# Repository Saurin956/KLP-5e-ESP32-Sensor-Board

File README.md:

# KLP-5e ESP32-C3 Sensor Board

> **Learning Recreation Project**

This is a learning recreation of the **KLP-5e ESP32-C3 4-layer IoT sensor board**. The schematic and PCB were recreated in KiCad by following the **Tech Explorations** tutorial. The resulting design closely follows the original reference project and was created to gain hands-on experience with a professional multilayer PCB design workflow.

## Project Status

* [x] Schematic recreated
* [x] 4-layer PCB layout completed
* [x] Design Rule Check (DRC) completed
* [x] Gerber and drill files generated
* [x] DFM/Gerber review completed
* [ ] PCB manufactured
* [ ] Hardware assembled
* [ ] Hardware tested

> The PCB design is complete, but this recreation has **not yet been manufactured, assembled, or hardware tested by me**.

## Overview

This project focuses on learning professional **4-layer PCB design** using KiCad through the recreation of an ESP32-C3 based IoT development board. The design integrates wireless connectivity, battery charging, environmental sensing, storage interfaces, display connectivity, and power management into a compact multilayer PCB.

The objective of this project was to understand the complete PCB design workflow, including schematic capture, component placement, multilayer routing, design validation, and manufacturing file generation.

## Board Features

* ESP32-C3-02 microcontroller with Wi-Fi and Bluetooth Low Energy
* 4-layer PCB stackup
* USB-C connector for power and programming interface
* TP4056 single-cell Li-ion battery charging circuit
* LiPo battery connector
* BME280 temperature, humidity, and pressure sensor
* Ambient light sensing
* Sound sensing circuit
* MicroSD card interface for data storage
* External flash memory
* I²C OLED display interface
* GPIO expansion interfaces
* Status LEDs and boot/reset circuitry
* Generated Gerber and drill files for manufacturing

## Learning Objectives

During this project, I practiced and learned:

* KiCad schematic design
* Hierarchical schematic organization
* 4-layer PCB stackup design
* Component placement and footprint selection
* Power distribution and grounding
* Decoupling capacitor placement
* Signal routing across multiple copper layers
* I²C and SPI peripheral integration
* USB and power management layout considerations
* Design Rule Checking (DRC)
* Gerber generation
* Drill file generation
* Design for Manufacturing (DFM) review

## Repository Structure

```text
.
├── Images/
│   └── PCB-3DView.png
│
├── KiCad 9 Esp32 Demo Project.kicad_pro
├── KiCad 9 Esp32 Demo Project.kicad_sch
├── KiCad 9 Esp32 Demo Project.kicad_pcb
│
├── esp32-c3-02.kicad_sch
├── sensors.kicad_sch
├── user_interface.kicad_sch
│
├── dfm/
│   └── gerber/
│
└── Esp32Project/
    └── Manufacturing output files
```

## Manufacturing Files

The repository includes generated manufacturing outputs such as:

* Gerber copper layers
* Solder mask layers
* Silkscreen layers
* Paste layers
* Board outline
* PTH and NPTH drill files
* Gerber job file

These files were generated as part of the KiCad PCB design workflow and reviewed during the learning exercise.

## Tools Used

* **KiCad 10** (project originally started in KiCad 9)
* ESP32-C3 hardware platform
* PCB Layout Editor
* Schematic Editor
* Gerber Viewer
* DRC and DFM tools

## Credits

This project is a **learning recreation** based on the original **KLP-5e ESP32-C3 Sensor Board** and the accompanying KiCad tutorial by **Tech Explorations (Peter Dalmaris)**.

* Original tutorial: Tech Explorations
* Original reference repository: `futureshocked/KLP-5e-ESP32-sensor-board`

I do **not** claim the original circuit or PCB design as my own. This repository documents my recreation and learning process using KiCad. The original project includes further design improvements, manufacturing, assembly, and hardware testing that are not yet part of my recreation.

## Future Work

* Make design improvements and explore possible modifications
* Manufacture the PCB
* Assemble the components
* Perform bring-up and hardware testing
* Validate power, charging, sensors, and storage interfaces
* Document testing results and board photographs

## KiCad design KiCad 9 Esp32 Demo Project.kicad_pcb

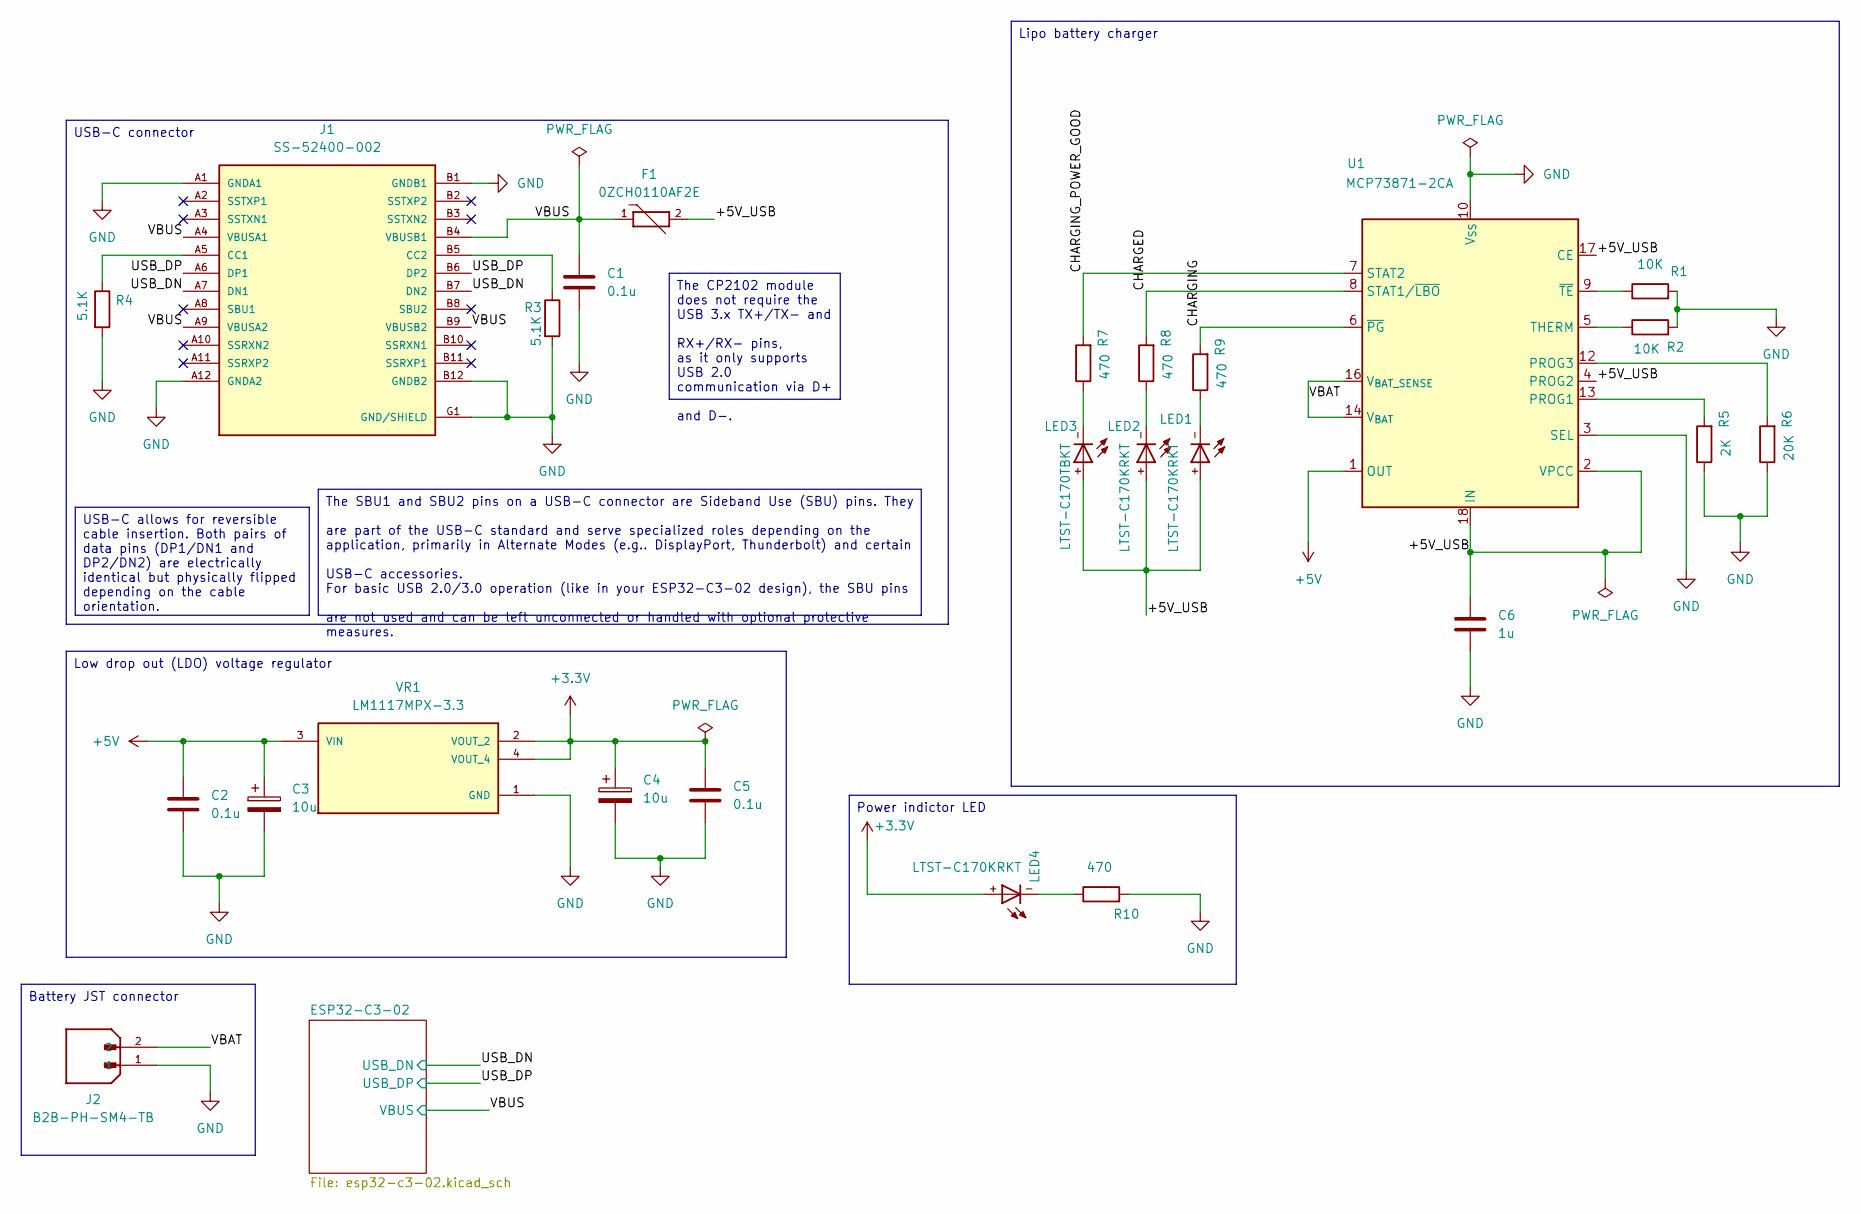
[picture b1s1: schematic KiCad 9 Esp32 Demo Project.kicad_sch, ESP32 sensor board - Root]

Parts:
C1, C2, C5: 0.1u; C_0805_2012Metric
C3, C4: 10u; T491A
C6: 1u; C_0805_2012Metric
F1: 0ZCH0110AF2E; FUSC3225X100N; PARTREV Apr2023; DigiKey_Part_Number 5923-0ZCH0110AF2ECT-ND
J1: SS-52400-002; BELFUSE_SS-52400-002; PARTREV A0
J2: B2B-PH-SM4-TB; JST_B2B-PH-SM4-TB; PARTREV N/A; DigiKey_Part_Number 455-B2B-PH-SM4-TBCT-ND
LED1, LED2, LED4: LTST-C170KRKT; LED_0805_2012Metric_My
LED3: LTST-C170TBKT; LED_0805_2012Metric_My
R1, R2: 10K; R_0805_2012Metric
R3, R4: 5.1K; R_0805_2012Metric
R5: 2K; R_0805_2012Metric
R6: 20K; R_0805_2012Metric
R7, R8, R9, R10: 470; R_0805_2012Metric
U1: MCP73871-2CA; QFN-20-1EP_4x4mm_P0.5mm_EP2.5x2.5mm
VR1: LM1117MPX-3.3; VREG_LM1117MPX-3.3; PARTREV O

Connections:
+3.3V: C4.1, C5.1, LED4.+, VR1.2 (VOUT_2), VR1.4 (VOUT_4); also elsewhere on the board
+5V: C2.1, C3.1, U1.1 (OUT), U1.20 (OUT), VR1.3 (VIN)
/+5V_USB: C6.1, F1.2, LED1.+, LED2.+, LED3.+, U1.2 (VPCC), U1.4 (PROG2), U1.17 (CE), U1.18 (IN), U1.19 (IN)
/CHARGED: R8.2, U1.8 (STAT1/~LBO)
/CHARGING: R9.2, U1.6 (~PG)
/CHARGING_POWER_GOOD: R7.2, U1.7 (STAT2)
/USB_DN: J1.A7 (DN1), J1.B7 (DN2); also elsewhere on the board
/USB_DP: J1.A6 (DP1), J1.B6 (DP2); also elsewhere on the board
/VBAT: J2.2, U1.14 (V_{BAT}), U1.15 (V_{BAT}), U1.16 (V_{BAT_SENSE})
/VBUS: C1.1, F1.1, J1.A4 (VBUSA1), J1.A9 (VBUSA2), J1.B4 (VBUSB1), J1.B9 (VBUSB2); also elsewhere on the board
GND: C1.2, C2.2, C3.2, C4.2, C5.2, C6.2, J1.A1 (GNDA1), J1.A12 (GNDA2), J1.B1 (GNDB1), J1.B12 (GNDB2), J1.G1 (GND/SHIELD), J1.G2 (GND/SHIELD), J1.G3 (GND/SHIELD), J1.G4 (GND/SHIELD), J1.S1 (GND/SHIELD), J1.S2 (GND/SHIELD), J1.S3 (GND/SHIELD), J1.S4 (GND/SHIELD), J2.1, R1.2, R2.2, R3.2, R4.2, R5.1, R6.1, R10.2, U1.3 (SEL), U1.10 (V_{SS}), U1.11 (V_{SS}), U1.21 (V_{SS}), VR1.1 (GND); also elsewhere on the board
unnamed: J1.A5 (CC1), R4.1
unnamed: J1.B5 (CC2), R3.1
unnamed: LED1.-, R9.1
unnamed: LED2.-, R8.1
unnamed: LED3.-, R7.1
unnamed: LED4.-, R10.1
unnamed: R5.2, U1.13 (PROG1)
unnamed: R6.2, U1.12 (PROG3)
unnamed: R2.1, U1.5 (THERM)
unnamed: R1.1, U1.9 (~TE)

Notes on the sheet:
USB-C connector
Lipo battery charger
The SBU1 and SBU2 pins on a USB-C connector are Sideband Use (SBU) pins. They are part of the USB-C standard and serve specialized roles depending on the application, primarily in Alternate Modes (e.g.. DisplayPort, Thunderbolt) and certain USB-C accessories. For basic USB 2.0/3.0 operation (like i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
Low drop out (LDO) voltage regulator
USB-C allows for reversible cable insertion. Both pairs of data pins (DP1/DN1 and DP2/DN2) are electrically identical but physically flipped depending on the cable orientation.
Battery JST connector
Power indictor LED
The CP2102 module does not require the USB 3.x TX+/TX- and RX+/RX- pins, as it only supports USB 2.0 communication via D+ and D-.

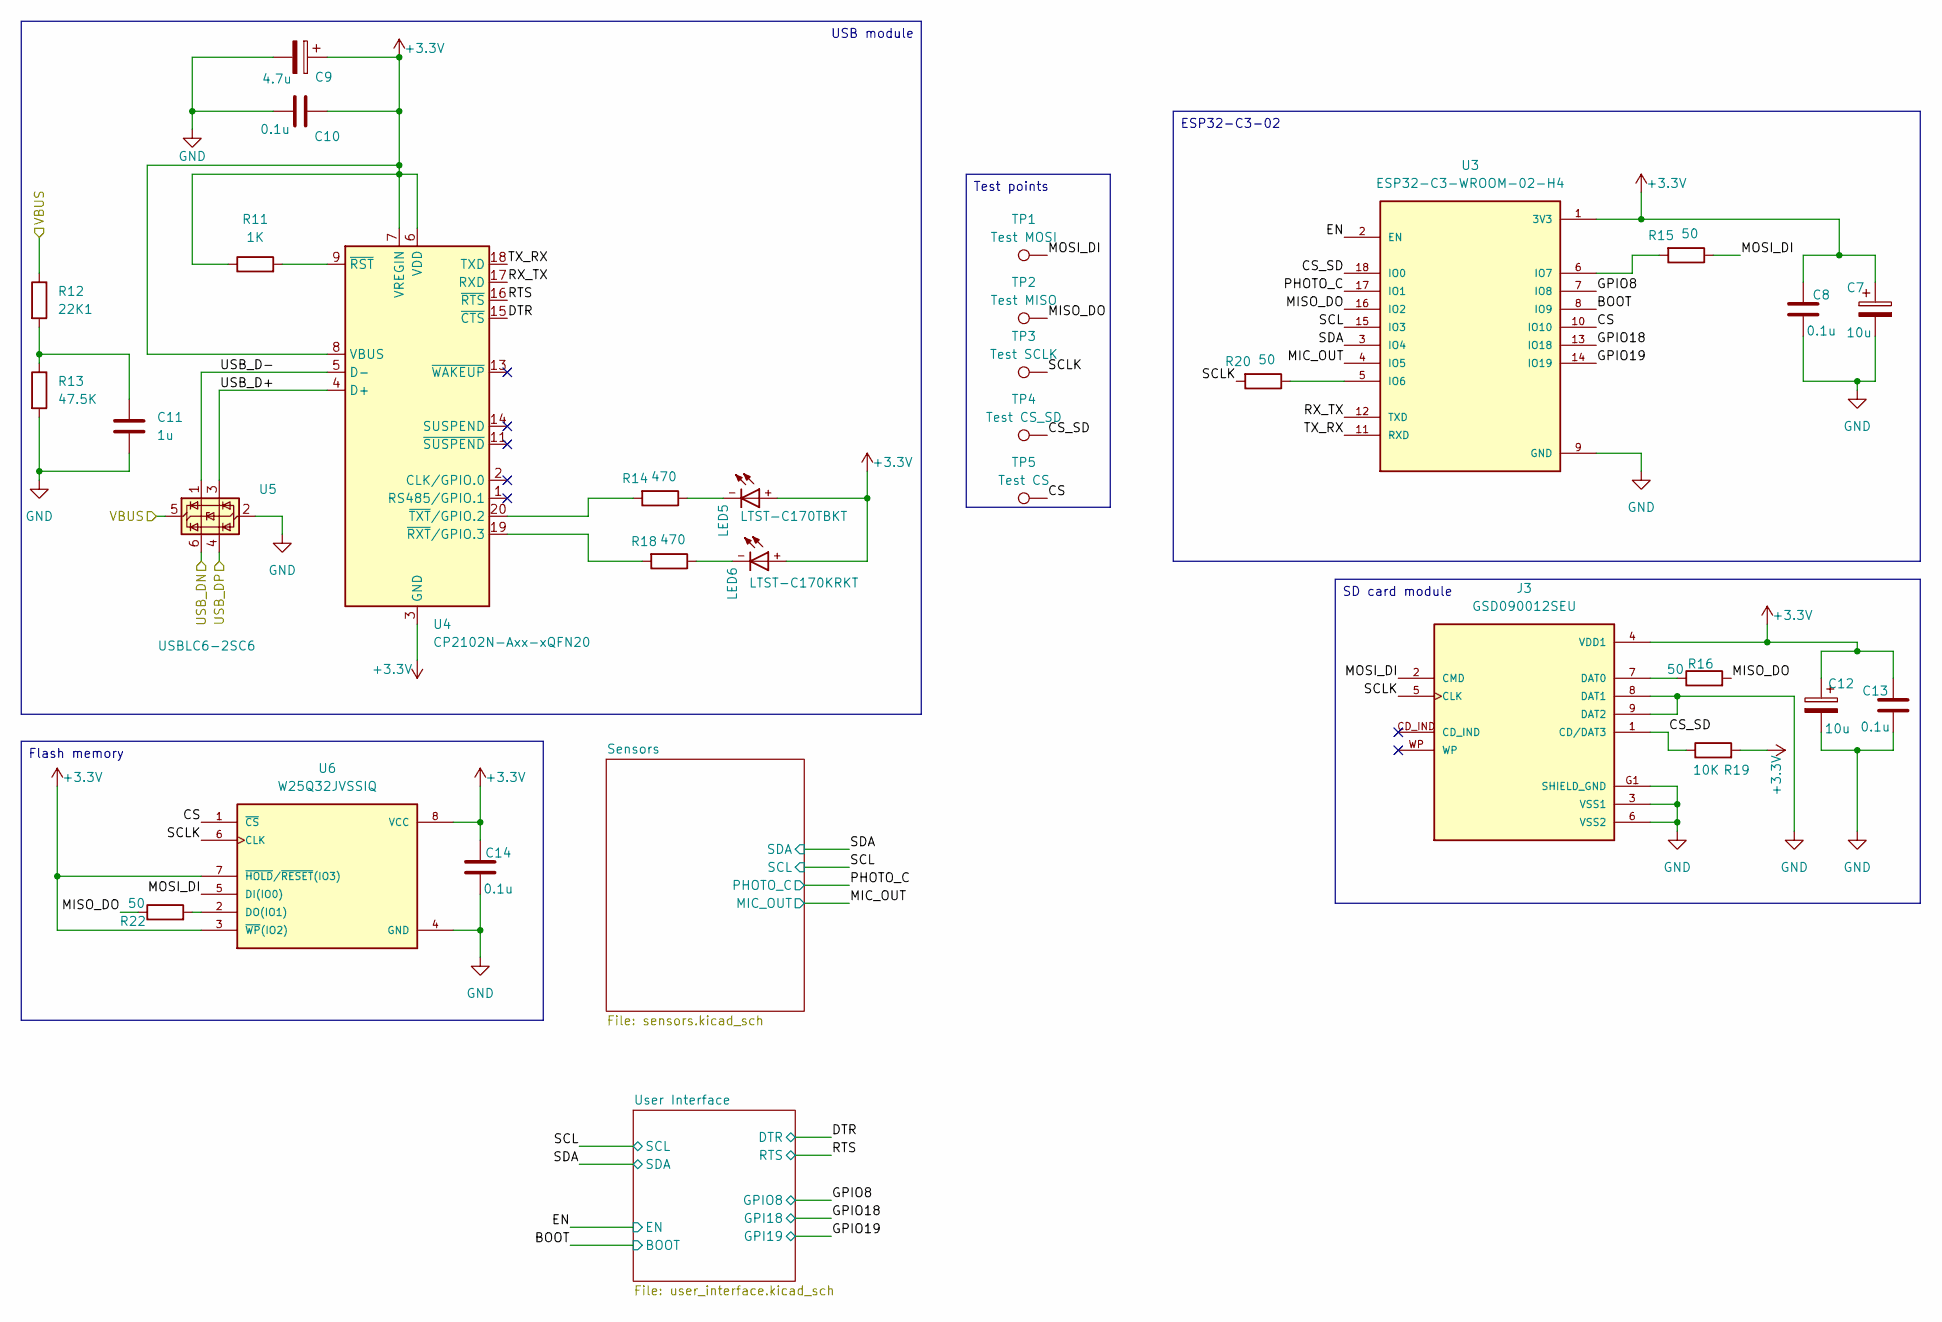
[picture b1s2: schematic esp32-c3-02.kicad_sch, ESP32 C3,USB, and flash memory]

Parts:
C7, C12: 10u; T491A
C8, C10, C13, C14: 0.1u; C_0805_2012Metric
C9: 4.7u; T491A
C11: 1u; C_0805_2012Metric
J3: GSD090012SEU; AMPHENOL_GSD090012SEU; PARTREV E
LED5: LTST-C170TBKT; LED_0805_2012Metric_My
LED6: LTST-C170KRKT; LED_0805_2012Metric_My
R11: 1K; R_0805_2012Metric
R12: 22K1; R_0805_2012Metric
R13: 47.5K; R_0805_2012Metric
R14, R18: 470; R_0805_2012Metric
R15, R16, R20, R22: 50; R_0805_2012Metric
R19: 10K; R_0805_2012Metric
TP1: Test MOSI; TestPoint_Pad_D1.0mm
TP2: Test MISO; TestPoint_Pad_D1.0mm
TP3: Test SCLK; TestPoint_Pad_D1.0mm
TP4: Test CS_SD; TestPoint_Pad_D1.0mm
TP5: Test CS; TestPoint_Pad_D1.0mm
U3: ESP32-C3-WROOM-02-H4; MODULE_ESP32-C3-WROOM-02-H4; DigiKey_Part_Number 1965-ESP32-C3-WROOM-02-H4CT-ND
U4: CP2102N-Axx-xQFN20; SiliconLabs_QFN-20-1EP_3x3mm_P0.5mm_EP1.8x1.8mm
U5: USBLC6-2SC6; SOT-23-6
U6: W25Q32JVSSIQ; SOIC127P790X216-8N; M_PART_NUMBER W25QXX

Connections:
+3.3V: C7.1, C8.2, C9.1, C10.2, C12.1, C13.2, C14.2, J3.4 (VDD1), LED5.+, LED6.+, R11.1, R19.2, U3.1 (3V3), U4.3 (GND), U4.6 (VDD), U4.7 (VREGIN), U4.8 (VBUS), U4.12 (GND), U4.21 (GND), U6.3 (~WP(IO2)), U6.7 (~HOLD/~RESET(IO3)), U6.8 (VCC); also elsewhere on the board
/ESP32-C3-02/BOOT: U3.8 (IO9); also elsewhere on the board
/ESP32-C3-02/CS: TP5.1, U3.10 (IO10), U6.1 (~CS)
/ESP32-C3-02/CS_SD: J3.1 (CD/DAT3), R19.1, TP4.1, U3.18 (IO0)
/ESP32-C3-02/DTR: U4.15 (~CTS); also elsewhere on the board
/ESP32-C3-02/EN: U3.2 (EN); also elsewhere on the board
/ESP32-C3-02/GPIO8: U3.7 (IO8); also elsewhere on the board
/ESP32-C3-02/GPIO18: U3.13 (IO18); also elsewhere on the board
/ESP32-C3-02/GPIO19: U3.14 (IO19); also elsewhere on the board
/ESP32-C3-02/MIC_OUT: U3.4 (IO5); also elsewhere on the board
/ESP32-C3-02/MISO_DO: R16.2, R22.1, TP2.1, U3.16 (IO2)
/ESP32-C3-02/MOSI_DI: J3.2 (CMD), R15.1, TP1.1, U6.5 (DI(IO0))
/ESP32-C3-02/PHOTO_C: U3.17 (IO1); also elsewhere on the board
/ESP32-C3-02/RTS: U4.16 (~RTS); also elsewhere on the board
/ESP32-C3-02/RX_TX: U3.12 (TXD), U4.17 (RXD)
/ESP32-C3-02/SCL: U3.15 (IO3); also elsewhere on the board
/ESP32-C3-02/SCLK: J3.5 (CLK), R20.2, TP3.1, U6.6 (CLK)
/ESP32-C3-02/SDA: U3.3 (IO4); also elsewhere on the board
/ESP32-C3-02/TX_RX: U3.11 (RXD), U4.18 (TXD)
/ESP32-C3-02/USB_D+: U4.4 (D+), U5.3 (I/O2)
/ESP32-C3-02/USB_D-: U4.5 (D-), U5.1 (I/O1)
/USB_DN: U5.6 (I/O1); also elsewhere on the board
/USB_DP: U5.4 (I/O2); also elsewhere on the board
/VBUS: R12.1, U5.5 (VBUS); also elsewhere on the board
GND: C7.2, C8.1, C9.2, C10.1, C11.2, C12.2, C13.1, C14.1, J3.3 (VSS1), J3.6 (VSS2), J3.8 (DAT1), J3.9 (DAT2), J3.G1 (SHIELD_GND), J3.G2 (SHIELD_GND), J3.G3 (SHIELD_GND), J3.G4 (SHIELD_GND), R13.2, U3.9 (GND), U3.19 (GND), U3.20 (GND), U3.21 (GND), U3.22 (GND), U3.23 (GND), U3.24 (GND), U3.25 (GND), U3.26 (GND), U3.27 (GND), U3.28 (GND), U3.29 (GND), U3.30 (GND), U3.31 (GND), U3.32 (GND), U3.33 (GND), U3.34 (GND), U3.35 (GND), U3.36 (GND), U3.37 (GND), U3.38 (GND), U3.39 (GND), U5.2 (GND), U6.4 (GND); also elsewhere on the board
unnamed: C11.1, R12.2, R13.1
unnamed: J3.7 (DAT0), R16.1
unnamed: LED5.-, R14.1
unnamed: LED6.-, R18.1
unnamed: R20.1, U3.5 (IO6)
unnamed: R15.2, U3.6 (IO7)
unnamed: R11.2, U4.9 (~RST)
unnamed: R18.2, U4.19 (~RXT/GPIO.3)
unnamed: R14.2, U4.20 (~TXT/GPIO.2)
unnamed: R22.2, U6.2 (DO(IO1))

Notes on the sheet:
ESP32-C3-02
SD card module
Flash memory
USB module
Test points

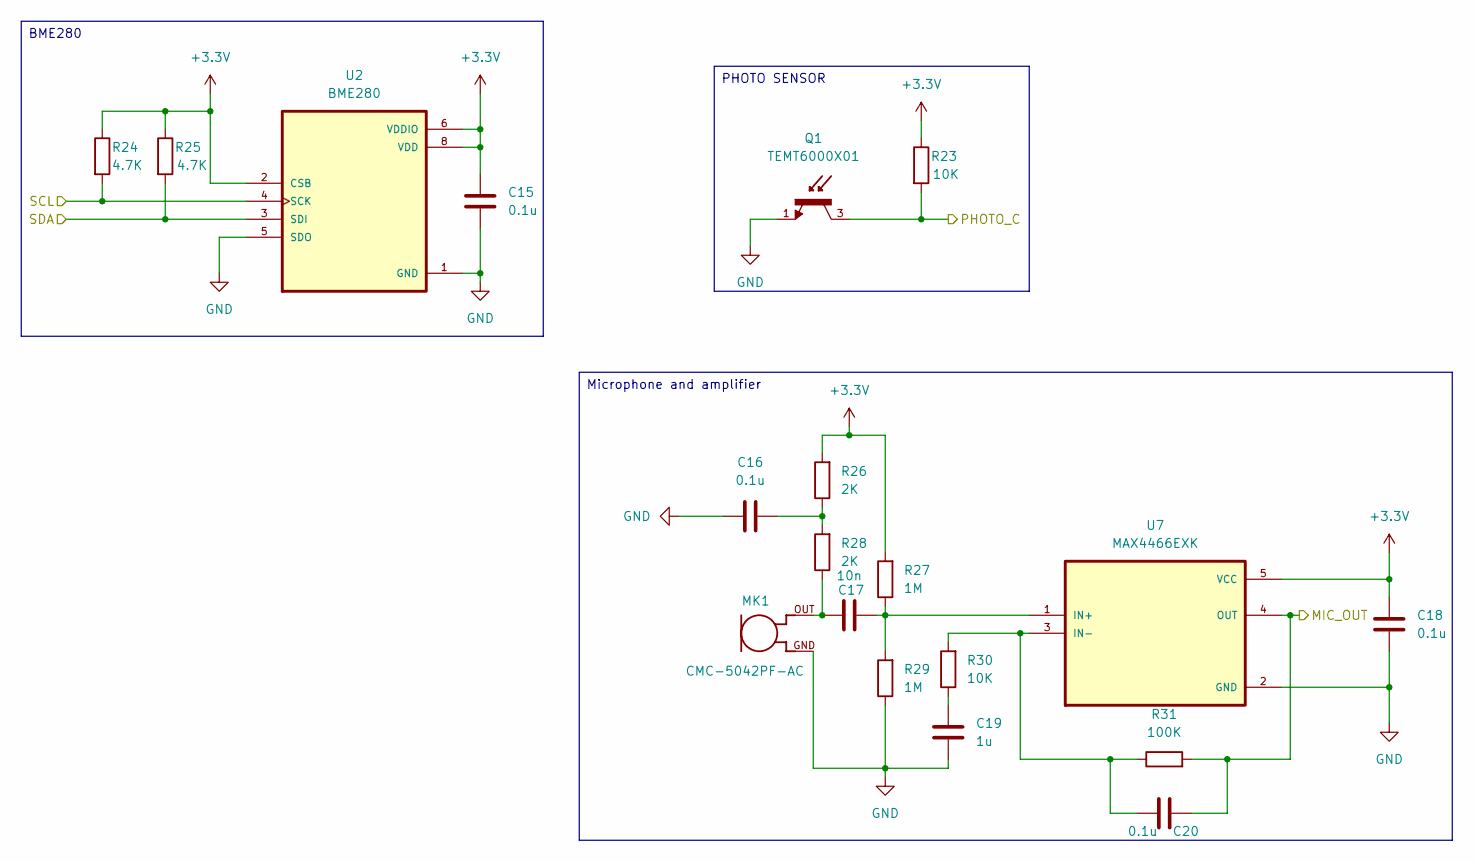
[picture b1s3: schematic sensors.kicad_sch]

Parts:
C15, C16, C18, C20: 0.1u; C_0805_2012Metric
C17: 10n; C_0805_2012Metric
C19: 1u; C_0805_2012Metric
MK1: CMC-5042PF-AC; CUI_CMC-5042PF-AC; DigiKey_Part_Number 102-1724-ND
Q1: TEMT6000X01; TRANS_TEMT6000X01; PARTREV 1.9; DigiKey_Part_Number 751-1055-1-ND
R23, R30: 10K; R_0805_2012Metric
R24, R25: 4.7K; R_0805_2012Metric
R26, R28: 2K; R_0805_2012Metric
R27, R29: 1M; R_0805_2012Metric
R31: 100K; R_0805_2012Metric
U2: BME280; PSON65P250X250X100-8N
U7: MAX4466EXK; SOT65P210X110-5N

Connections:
+3.3V: C15.1, C18.1, R23.1, R24.1, R25.1, R26.2, R27.2, U2.2 (CSB), U2.6 (VDDIO), U2.8 (VDD), U7.5 (VCC); also elsewhere on the board
/ESP32-C3-02/MIC_OUT: C20.2, R31.2, U7.4 (OUT); also elsewhere on the board
/ESP32-C3-02/PHOTO_C: Q1.3, R23.2; also elsewhere on the board
/ESP32-C3-02/SCL: R24.2, U2.4 (SCK); also elsewhere on the board
/ESP32-C3-02/SDA: R25.2, U2.3 (SDI); also elsewhere on the board
GND: C15.2, C16.2, C18.2, C19.1, MK1.GND, Q1.1, R29.1, U2.1 (GND), U2.5 (SDO), U2.7 (GND), U7.2 (GND); also elsewhere on the board
unnamed: C16.1, R26.1, R28.2
unnamed: C17.2, MK1.OUT, R28.1
unnamed: C19.2, R30.1
unnamed: C17.1, R27.1, R29.2, U7.1 (IN+)
unnamed: C20.1, R30.2, R31.1, U7.3 (IN-)

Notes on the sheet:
BME280
PHOTO SENSOR
Microphone and amplifier

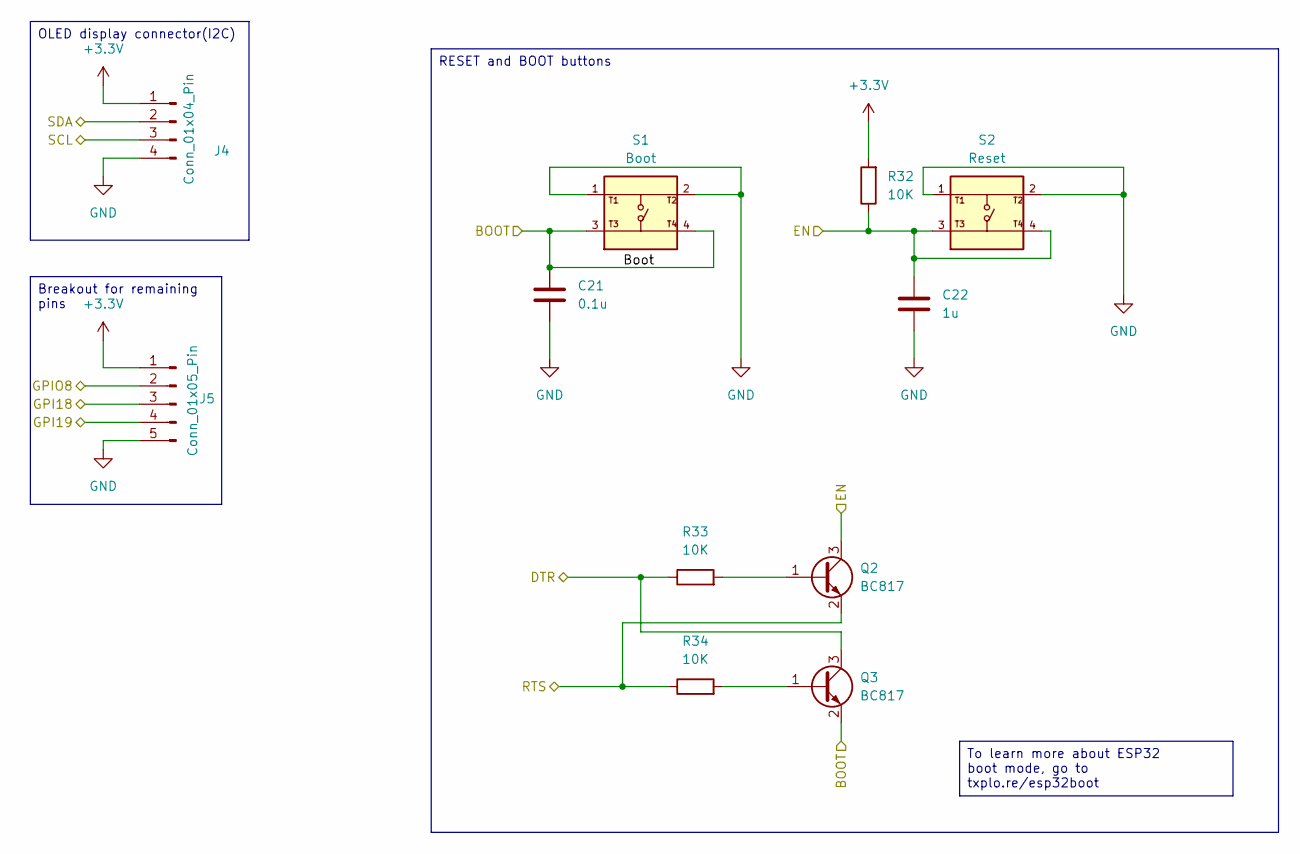
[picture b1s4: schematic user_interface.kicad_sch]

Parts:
C21: 0.1u; C_0805_2012Metric
C22: 1u; C_0805_2012Metric
J4: Conn_01x04_Pin; PinHeader_1x04_P2.54mm_Vertical
J5: Conn_01x05_Pin; PinHeader_1x05_P2.54mm_Vertical
Q2, Q3: BC817; SOT-23
R32, R33, R34: 10K; R_0805_2012Metric
S1: Boot; SW_USLPT2819DT2TR; PARTREV P; DigiKey_Part_Number 450-3358-1-ND
S2: Reset; SW_USLPT2819DT2TR; PARTREV P; DigiKey_Part_Number 450-3358-1-ND

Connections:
+3.3V: J4.1, J5.1, R32.2; also elsewhere on the board
/ESP32-C3-02/BOOT: C21.1, Q3.2 (E), S1.3, S1.4; also elsewhere on the board
/ESP32-C3-02/DTR: Q3.3 (C), R33.1; also elsewhere on the board
/ESP32-C3-02/EN: C22.1, Q2.3 (C), R32.1, S2.3, S2.4; also elsewhere on the board
/ESP32-C3-02/GPIO8: J5.2; also elsewhere on the board
/ESP32-C3-02/GPIO18: J5.3; also elsewhere on the board
/ESP32-C3-02/GPIO19: J5.4; also elsewhere on the board
/ESP32-C3-02/RTS: Q2.2 (E), R34.1; also elsewhere on the board
/ESP32-C3-02/SCL: J4.3; also elsewhere on the board
/ESP32-C3-02/SDA: J4.2; also elsewhere on the board
GND: C21.2, C22.2, J4.4, J5.5, S1.1, S1.2, S2.1, S2.2; also elsewhere on the board
unnamed: Q2.1 (B), R33.2
unnamed: Q3.1 (B), R34.2

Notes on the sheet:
RESET and BOOT buttons
Breakout for remaining pins
OLED display connector(I2C)
To learn more about ESP32 boot mode, go to txplo.re/esp32boot

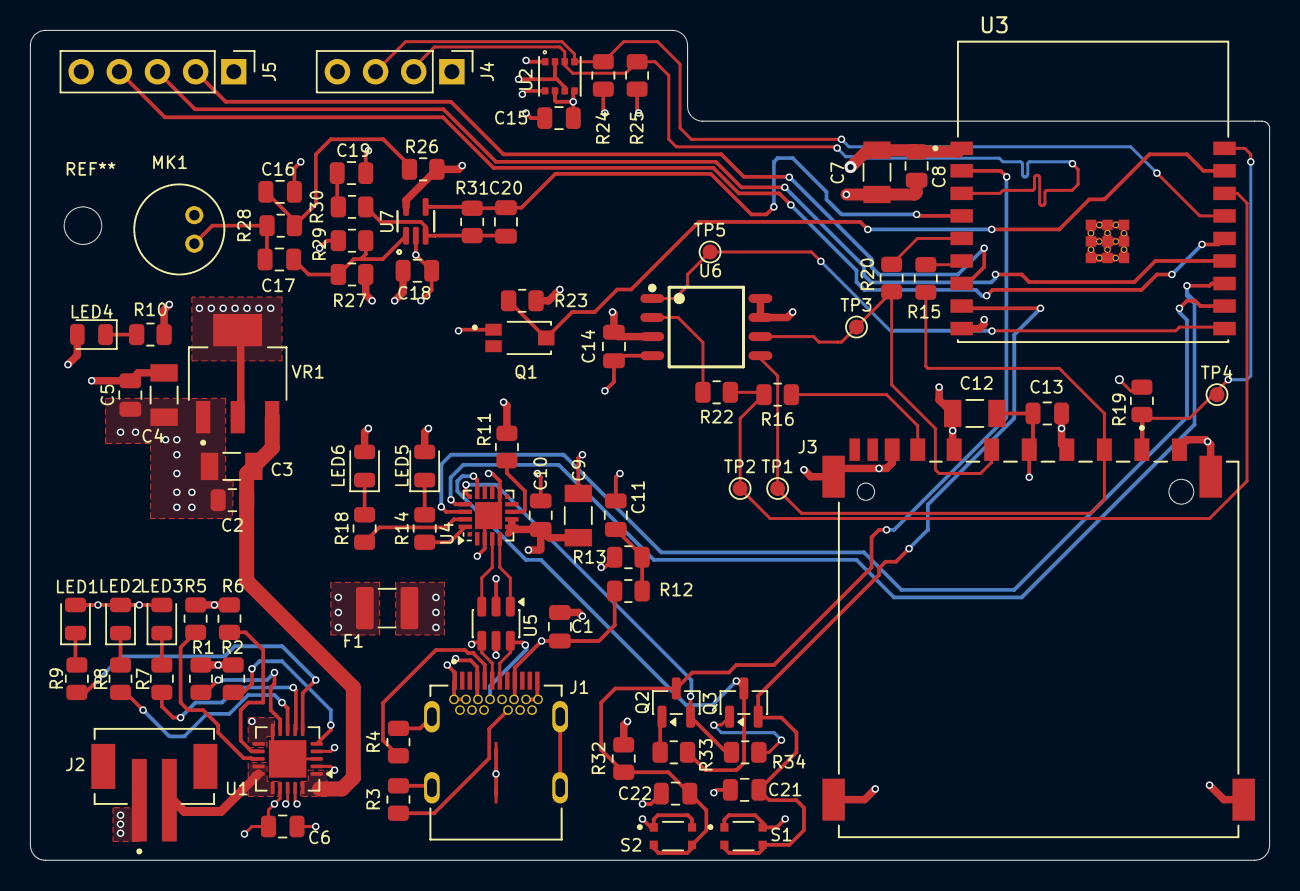
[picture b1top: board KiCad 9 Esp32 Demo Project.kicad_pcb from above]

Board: 4 copper layers, 82.5 x 55.2 mm, 85 parts (0 on the bottom side), 58 nets.
